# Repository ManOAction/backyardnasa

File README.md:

# Backyard NASA Rover Project
I figured making a robot rover that lived on its own somewhere and sent pictures of
rocks back to me couldn't be that hard if the gubberment folks at NASA could do it.

Her name is Matilda, and this is her story.

We started using this tutorial.
https://projects.raspberrypi.org/en/projects/physical-computing/3

New Documentation is being implemented here in Notion:
https://www.notion.so/Matilda-4c2012eff4d847c4a76360bea5a4a66a

# ChangeLog
2021-10-29, JDL -- Oh man, it's been a long time.  Moving docs to Notion and learning ROS
2020-12-27, JDL -- Updating diary and writing new roadmap for 2021
2020-07-26, JDL -- Motors, Atmo, Sonic, and Magna systems are all working.
2020-07-25, JDL -- Starting it up again.  Stuff's broke.
2020-02-22, JDL -- Rover Patterns, Temp Sensors, and Chat Capabilities
2019-11-18, JDL -- First Draft

# TODO
  Now being tracked in the "Current Roadmap Section"

# Other Ideas
Automatic Hard Iron Offset Recalibration: Use the magnet calibrator logic in the middle of
    360 turning to reset and reassign offset variables.

# Changes from Stock Raspian Setup
############################################################

We're reconfiguring the Pi to enable I2C and adding it to the kernal.
https://www.instructables.com/id/Raspberry-Pi-I2C-Python/
Note: When it says "i2cdetect -y 0" you need to say "i2c detect -y 1"

We're using an ancient library with docs listed here. (got to be something better)
http://wiki.erazor-zone.de/wiki:linux:python:smbus:doc

Following this to enable the SPI bus.
https://tutorials-raspberrypi.com/infrared-distance-measurement-with-the-raspberry-pi-sharp-gp2y0a02yk0f/

# Misc Thoughts
###########################################################

Check Bot Secrets for API info related to Chatbots

Use i2cdetect -y 1 to confirm I2C connections

Current board is loaded up on a Pi B+
pi@192.168.122.195 was the last known location
-u pi -p raspberry

##########################################################

# Broad Roadmap
##########################################################

Phase I: Basic Capabilities:
  - Pictures of Objects
  - Geofencing
  - Talking to Slack Channel  
  - Passive Charging and Voltage Checking

Phase II: Initial Backyard Trials
  - Success after multiple days of continuous operation achieved

Phase III: Scale to Pasture Size
  - Build to "coffee table" size

Phase IV: Profit?

# Current Roadmap (Newly drafted on 12/27)
##########################################################

Separate Motor Power Supply
  - This means having the computer run on a self contained system away from the
  drive motors.

  - Twin Sonic Sensors (HCSR04) for the left and right bumpers.

  - Functioning camera module that talks to a social account (slack?)

  - Update 3D printed housing for sensors, Pi, and batteries.

  - Capable of autonomous functioning until batteries deplete themselves.

# Diary
##########################################################

12/27, JDL - After lying dormant for months, matilda boots and runs fine, but the motors and power issue
  remain an issue.   I'm going to pursue using a NiMH battery to power the motors with a MOSFET in between
  to turn the battery on and off.  It looks like charging NiMH is a bit of a pain, but we're going to move
  forward with it since it's what we've got.   Passive charging/recharging may be a feature that is a long
  ways down the road.  We may as well get it to function long enough to deplete it's batteries before we try
  to learn how to recharge it.

7/26, JDL - I got tripped up on BCM/DPI pin numbering and it took a long time to fix.  Everything's working
  right now.  I'm going to clean up the codebase and then move on to a new feature to add.

7/26, JDL - This is dumb.  After looking at the official CircuitPython libraries for the HCSR04, they
  just have a poor feature set compared to this guy's custom one.  https://github.com/MarkAHeywood/Bluetin_Python_Echo
  I'm switching back to using it.

7/25, JDL - Starting back into it, and stuff's broke as we were mixed up between the Blinka library
  from Adafruit and the old stuff we had.  Frustrated because it was working until I patched a change.
  Locomotion is the only thing working and it only works at low voltage (<5V).  I need to find if I
  can use capacitors or something else to prevent the battery from shorting anytime I want more
  voltage from it.  Trying to start piece by piece putting things back online.

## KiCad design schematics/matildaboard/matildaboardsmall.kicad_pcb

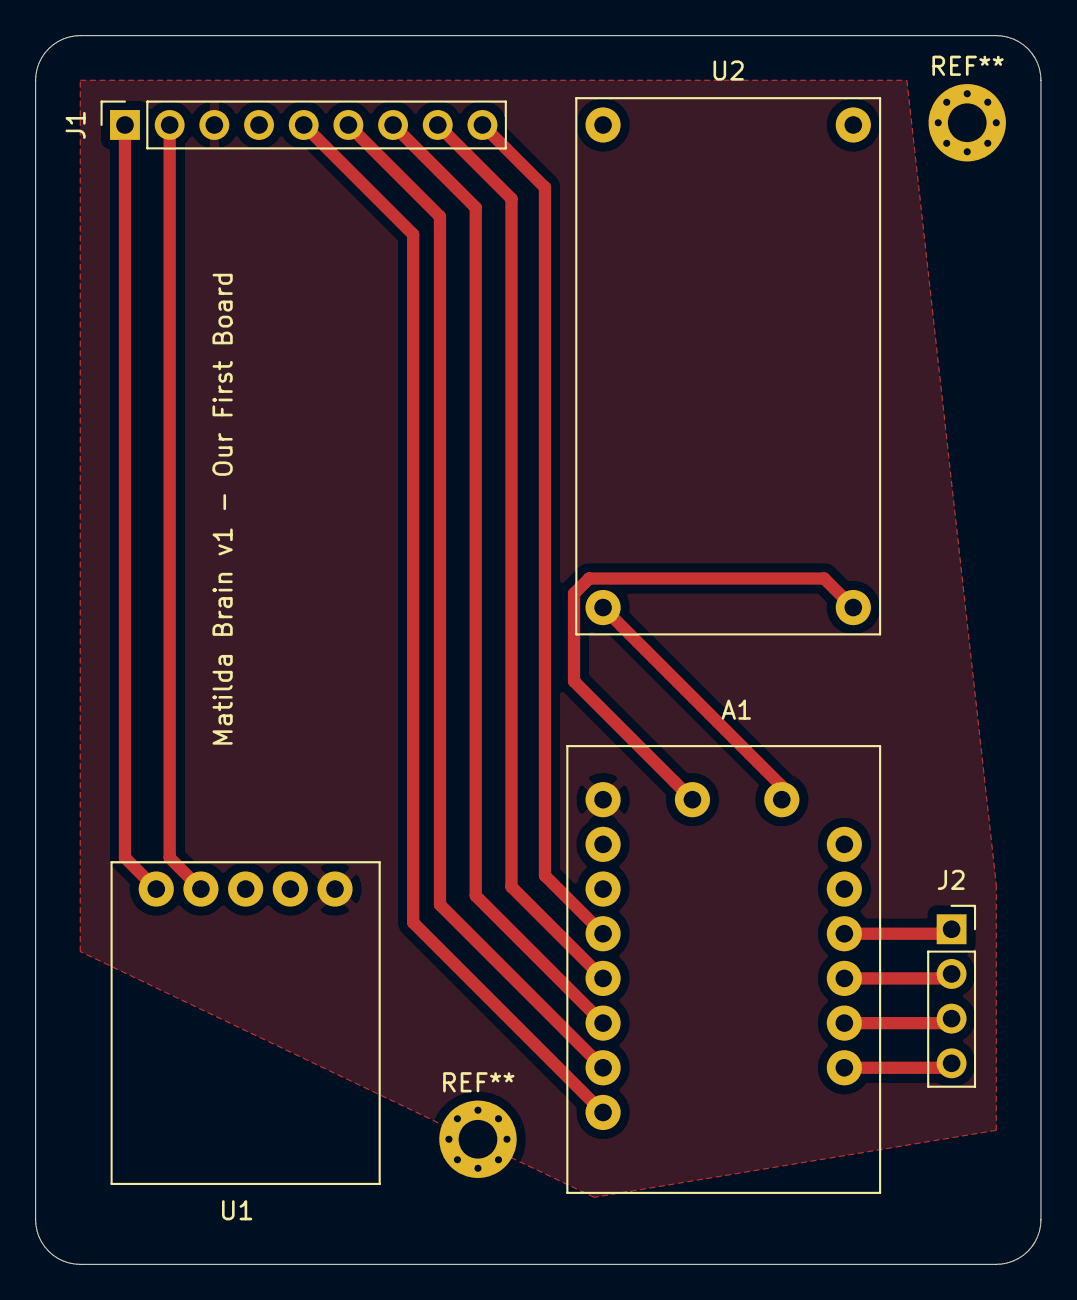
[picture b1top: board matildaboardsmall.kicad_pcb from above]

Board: 2 copper layers, 57.2 x 69.9 mm, 5 parts (0 on the bottom side), 15 nets.

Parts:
A1: Adafruit_Breakout_DRV8833
J1: Conn_01x09_Female; PinSocket_1x09_P2.54mm_Vertical
J2: Conn_01x04_Female; PinSocket_1x04_P2.54mm_Vertical
U1: AdaBrk_Si7021; Adafruit_Si7021_Breakout
U2: Woo_StepUp_MT3608

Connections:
3.3V: A1.1, J1.3, U1.1
GND: A1.2, J1.4, U1.3
Logic_1: A1.8, J1.5
Logic_2: A1.7, J1.6
Logic_3: A1.6, J1.7
Logic_4: A1.5, J1.8
Logic_5: A1.4, J1.9
unnamed: A1.9, J2.4
unnamed: A1.10, J2.3
unnamed: A1.11, J2.2
unnamed: A1.12, J2.1
unnamed: A1.15, U2.3
unnamed: A1.16, U2.4
SCL: J1.2, U1.4
SDA: J1.1, U1.5

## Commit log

2020-02-13 Update blink.py
    Closing the docstring so we aren't behaving like barbarians.
2020-02-13 Updating readme and testing. Can anybody just commit to the master?
2020-02-13 Testing how to push.
2020-02-15 comment edits
2020-02-15 Adding wiring schematics
2020-02-16 Big clean up and a stable build of the rover program.
2020-02-18 Adding motor speed variable to fix the drift in the motors.
2020-02-18 Dropping pipenv. It was just being a pain. Not enough dependencies to matter.
2020-02-19 Adding gitignore for secrets.
2020-02-19 testing
2020-02-19 fixing
2020-02-19 testing gitignore
2020-02-19 Twitter API now works for the chat concept
2020-02-19 updating gitignore
2020-02-20 shared drive issues
    shared drive issues
2020-02-22 Adding a chat loop and functionality for temp sensor.
    Temp Sensor and chat now working(ish)
2020-02-22 chat bot changes
    chat changes
2020-02-22 test
    test
2020-02-23 Incorporated atmo sensor into rover
    Incorporated atmo sensor into rover.
2020-02-24 updating chatbot test
    updating chatbot test
2020-02-24 Update rover.py
    Added error handling for command
2020-03-02 kiCAD Files for PCB
    Adding kiCAD Files for Eventual PCB
2020-03-07 Docs and Tweaks
    Adding printable files for brackets, and converting sensor libraries to Blinka.
2020-07-25 Fixing hunt, trying to unbreak Atmo Sensor.
2020-07-26 Patching a draft to a different machine.
2020-07-26 At this commit, locomotion and atmo are working. No distance yet.
2020-07-26 Posting sonicsensor.py to a forum for help.
2020-07-26 Fixed sonicsensor and hunt mode. Fixed magnometer to give a heading.
2020-07-26 Commenting and housekeeping.
2020-07-26 updating comments.
2020-07-27 tweaking chatbots.
2020-07-28 new gitignure
2020-07-28 ramblings about webhooks.
2020-12-28 Updating diary and roadmap.
2020-12-30 Implementing camera tests, and testing VS Code git
2020-12-30 Deploying for Testing
2021-02-01 Adding all kinds of gorgeous new brackets. Body style 1.0
2021-02-11 Chatbot updates, adding 2nd eye.
2021-11-04 Servoarmfix
2021-11-08 finalizing for merge
2021-11-08 testing git sparse checkout
2021-11-08 removing git checkout test
2021-11-08 building a new test.
2021-11-08 test
2021-11-16 Printables and testing movement
2021-11-16 typo fix
2021-11-29 adding a menu and attempting callback reference
2021-11-29 seperating rover node
2021-11-30 trying sid fabers motor class
2021-11-30 Testing New Sense Node
2021-11-30 bug fix
2021-11-30 bugfix
2021-11-30 typo
2021-11-30 tweak
2022-05-28 testing rebuild
2022-05-28 raspberry
2022-05-28 pin fixes
2023-03-07 ROS2 Setup
2023-03-07 gitignoreupdate
2023-03-07 moving stufff
2023-11-17 cleaning up
2023-11-18 updates...
2023-11-18 base app
